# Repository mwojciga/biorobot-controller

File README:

Written by:
Klaudia Trembecka
Maciej Wójciga

Copyright 2013

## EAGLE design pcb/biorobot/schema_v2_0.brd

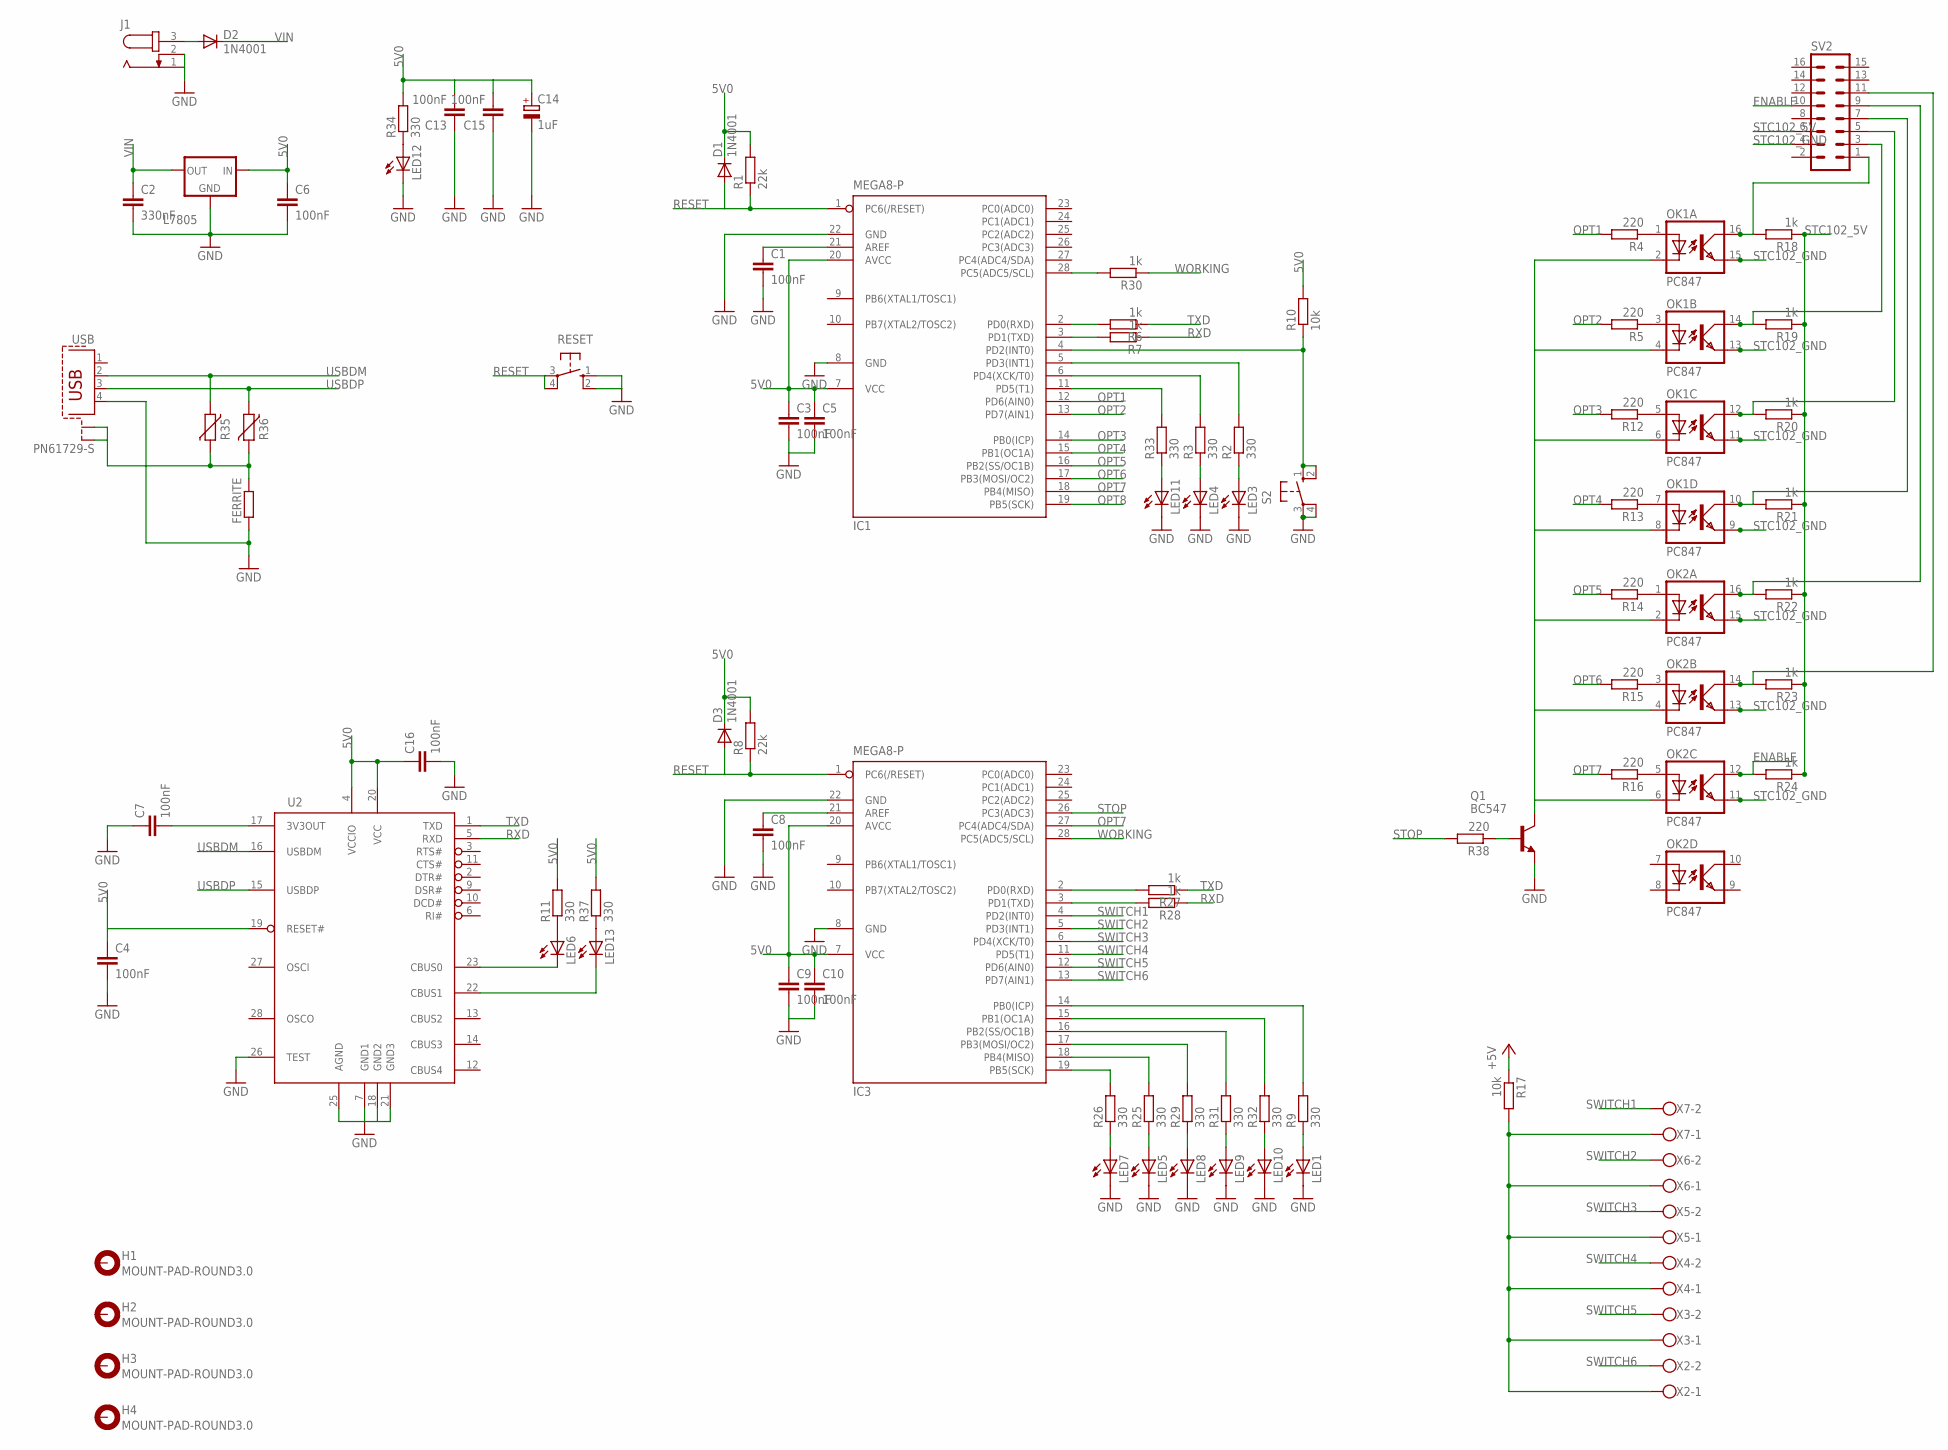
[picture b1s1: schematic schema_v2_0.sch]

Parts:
C1, C3, C5, C6, C8, C9, C10, C13, C15: 100nF; C025-025X050
C2: 330nF; C025-025X050
C4, C7, C16: 100nF; C0603K
C14: 1uF; E2,5-5
D1, D2, D3: 1N4001; DO41-10
FERRITE: R-EU_M0805; M0805
H1, H2, H3, H4: MOUNT-PAD-ROUND3.0; 3,0-PAD
IC1, IC3: MEGA8-P; DIL28-3
J1: JACK-PLUG0; SPC4077
L7805: 79XXS
LED1, LED3, LED4, LED5, LED6, LED7, LED8, LED9, LED10, LED11, LED12, LED13: LED3MM
OK1, OK2: PC847; DIL16
Q1: BC547; TO92
R1, R8: 22k; 0207/10
R2, R3, R9, R11, R25, R26, R29, R31, R32, R33, R34, R37: 330; 0207/10
R4, R5, R12, R13, R14, R15, R16, R38: 220; 0207/10
R6, R7, R27, R28, R30: 1k; M1206
R10, R17: 10k; 0207/10
R18, R19, R20, R21, R22, R23, R24: 1k; 0207/10
R35, R36: VARISTORCN0603; CT/CN0603
RESET: 10-XX; B3F-10XX
S2: 10-XX; B3F-10XX
SV2: MA08-2
U2: FT232RL; SSOP28DB
USB: PN61729-S
X2, X3, X4, X5, X6, X7: W237-102

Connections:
5V0: C3.1, C4.1, C5.1, C6.1, C9.1, C10.1, C13.2, C14.+, C15.2, C16.1, D1.C, D3.C, IC1.7 (VCC), IC1.20 (AVCC), IC3.7 (VCC), IC3.20 (AVCC), L7805.IN, R1.2, R8.2, R10.2, R11.2, R34.2, R37.2, U2.4 (VCCIO), U2.19 (RESET#), U2.20 (VCC)
+5V: R17.1
ENABLE: OK2.12 (COL), R24.2, SV2.10
GND: C1.2, C2.2, C3.2, C4.2, C5.2, C6.2, C7.1, C8.2, C9.2, C10.2, C13.1, C14.-, C15.1, C16.2, FERRITE.1, IC1.8 (GND), IC1.22 (GND), IC3.8 (GND), IC3.22 (GND), J1.1, J1.2, L7805.GND, LED1.K (C), LED3.K (C), LED4.K (C), LED5.K (C), LED7.K (C), LED8.K (C), LED9.K (C), LED10.K (C), LED11.K (C), LED12.K (C), Q1.1 (E), RESET.1 (S), RESET.2 (S1), S2.3, S2.4 (P1), U2.7 (GND1), U2.18 (GND2), U2.21 (GND3), U2.25 (AGND), U2.26 (TEST), USB.4
unnamed: LED1.A, R9.1
unnamed: C1.1, IC1.21 (AREF)
unnamed: IC1.6 (PD4(XCK/T0)), R3.2
unnamed: IC1.4 (PD2(INT0)), R10.1, S2.1 (S), S2.2 (S1)
unnamed: LED3.A, R2.1
unnamed: LED4.A, R3.1
unnamed: D2.A, J1.3
unnamed: OK1.16 (COL), R18.2, SV2.1
unnamed: IC1.5 (PD3(INT1)), R2.2
unnamed: OK1.14 (COL), R19.2, SV2.3
unnamed: OK1.12 (COL), R20.2, SV2.5
unnamed: OK1.10 (COL), R21.2, SV2.7
unnamed: OK2.16 (COL), R22.2, SV2.9
unnamed: OK2.14 (COL), R23.2, SV2.11
unnamed: C8.1, IC3.21 (AREF)
unnamed: LED6.K (C), U2.23 (CBUS0)
unnamed: LED13.K (C), U2.22 (CBUS1)
unnamed: LED6.A, R11.1
unnamed: IC3.14 (PB0(ICP)), R9.2
unnamed: IC1.28 (PC5(ADC5/SCL)), R30.2
unnamed: OK1.2 (C), OK1.4 (C), OK1.6 (C), OK1.8 (C), OK2.2 (C), OK2.4 (C), OK2.6 (C), Q1.3 (C)
unnamed: Q1.2 (B), R38.1
unnamed: IC1.2 (PD0(RXD)), R6.2
unnamed: IC1.3 (PD1(TXD)), R7.2
unnamed: OK1.1 (A), R4.1
unnamed: OK1.3 (A), R5.1
unnamed: OK1.5 (A), R12.1
unnamed: OK1.7 (A), R13.1
unnamed: OK2.1 (A), R14.1
unnamed: OK2.3 (A), R15.1
unnamed: OK2.5 (A), R16.1
unnamed: LED5.A, R25.1
unnamed: R17.2, X2.1, X3.1, X4.1, X5.1, X6.1, X7.1
unnamed: LED7.A, R26.1
unnamed: LED8.A, R29.1
unnamed: LED10.A, R32.1
unnamed: IC3.19 (PB5(SCK)), R26.2
unnamed: LED9.A, R31.1
unnamed: IC3.2 (PD0(RXD)), R27.2
unnamed: IC3.3 (PD1(TXD)), R28.2
unnamed: IC3.18 (PB4(MISO)), R25.2
unnamed: IC3.17 (PB3(MOSI/OC2)), R29.2
unnamed: IC3.16 (PB2(SS/OC1B)), R31.2
unnamed: IC3.15 (PB1(OC1A)), R32.2
unnamed: LED11.A, R33.1
unnamed: IC1.11 (PD5(T1)), R33.2
unnamed: LED12.A, R34.1
unnamed: FERRITE.2, R35.2, R36.2, USB.S1, USB.S2
unnamed: LED13.A, R37.1
unnamed: C7.2, U2.17 (3V3OUT)
OPT1: IC1.12 (PD6(AIN0)), R4.2
OPT2: IC1.13 (PD7(AIN1)), R5.2
OPT3: IC1.14 (PB0(ICP)), R12.2
OPT4: IC1.15 (PB1(OC1A)), R13.2
OPT5: IC1.16 (PB2(SS/OC1B)), R14.2
OPT6: IC1.17 (PB3(MOSI/OC2)), R15.2
OPT7: IC1.18 (PB4(MISO)), IC3.27 (PC4(ADC4/SDA)), R16.2
OPT8: IC1.19 (PB5(SCK))
RESET: D1.A, D3.A, IC1.1 (PC6(/RESET)), IC3.1 (PC6(/RESET)), R1.1, R8.1, RESET.3, RESET.4 (P1)
RXD: R7.1, R28.1, U2.5 (RXD)
STC102_5V: R18.1, R19.1, R20.1, R21.1, R22.1, R23.1, R24.1, SV2.6
STC102_GND: OK1.9 (EMIT), OK1.11 (EMIT), OK1.13 (EMIT), OK1.15 (EMIT), OK2.11 (EMIT), OK2.13 (EMIT), OK2.15 (EMIT), SV2.4
STOP: IC3.26 (PC3(ADC3)), R38.2
SWITCH1: IC3.4 (PD2(INT0)), X7.2
SWITCH2: IC3.5 (PD3(INT1)), X6.2
SWITCH3: IC3.6 (PD4(XCK/T0)), X5.2
SWITCH4: IC3.11 (PD5(T1)), X4.2
SWITCH5: IC3.12 (PD6(AIN0)), X3.2
SWITCH6: IC3.13 (PD7(AIN1)), X2.2
TXD: R6.1, R27.1, U2.1 (TXD)
USBDM: R35.1, U2.16 (USBDM), USB.2
USBDP: R36.1, U2.15 (USBDP), USB.3
VIN: C2.1, D2.C, L7805.OUT
WORKING: IC3.28 (PC5(ADC5/SCL)), R30.1

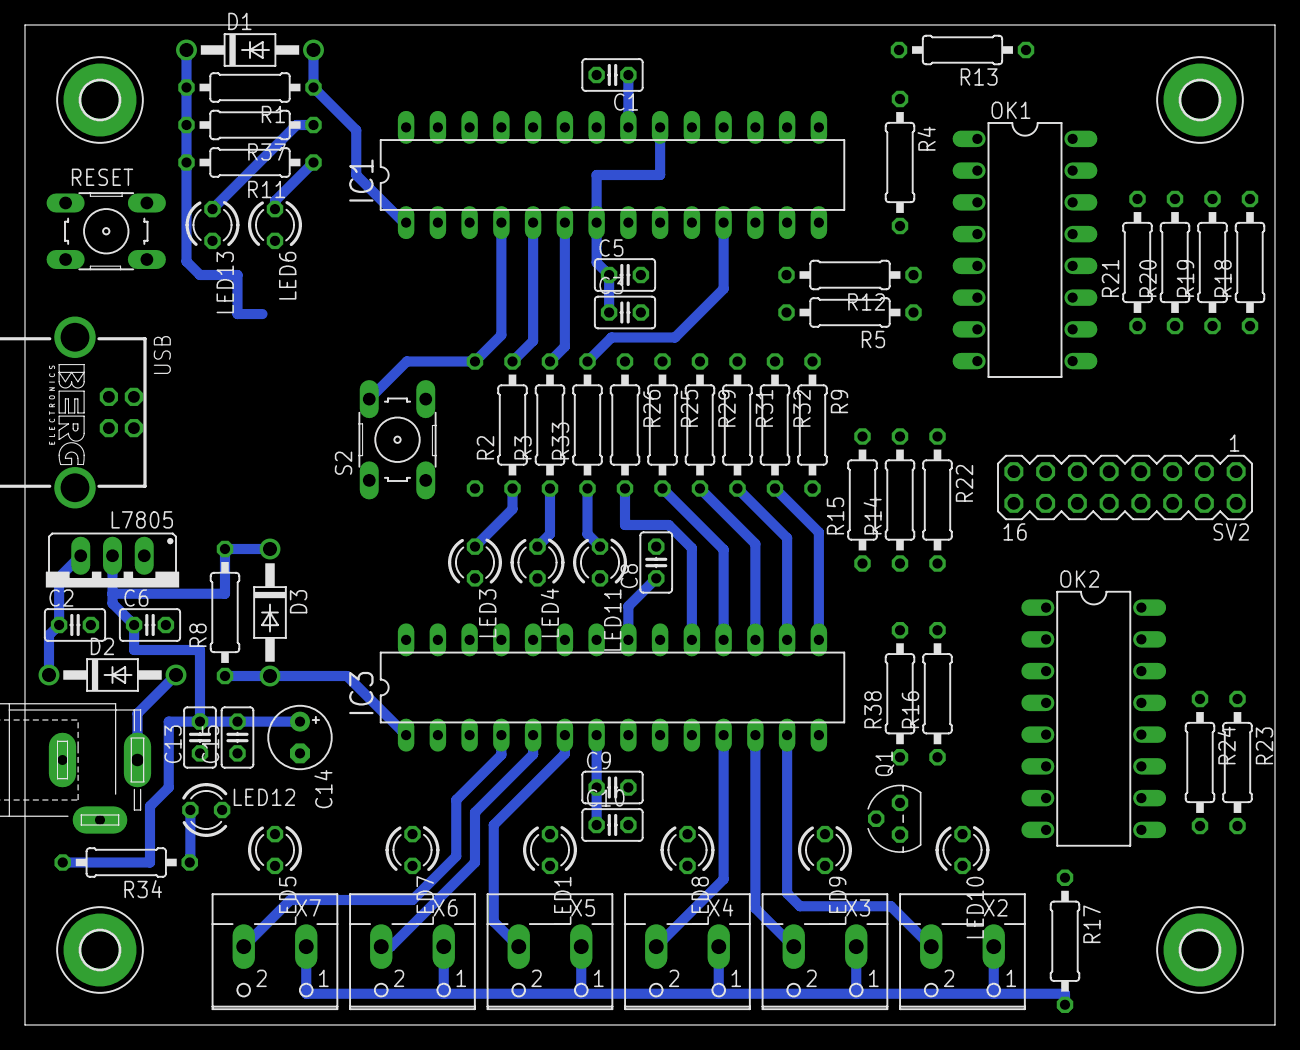
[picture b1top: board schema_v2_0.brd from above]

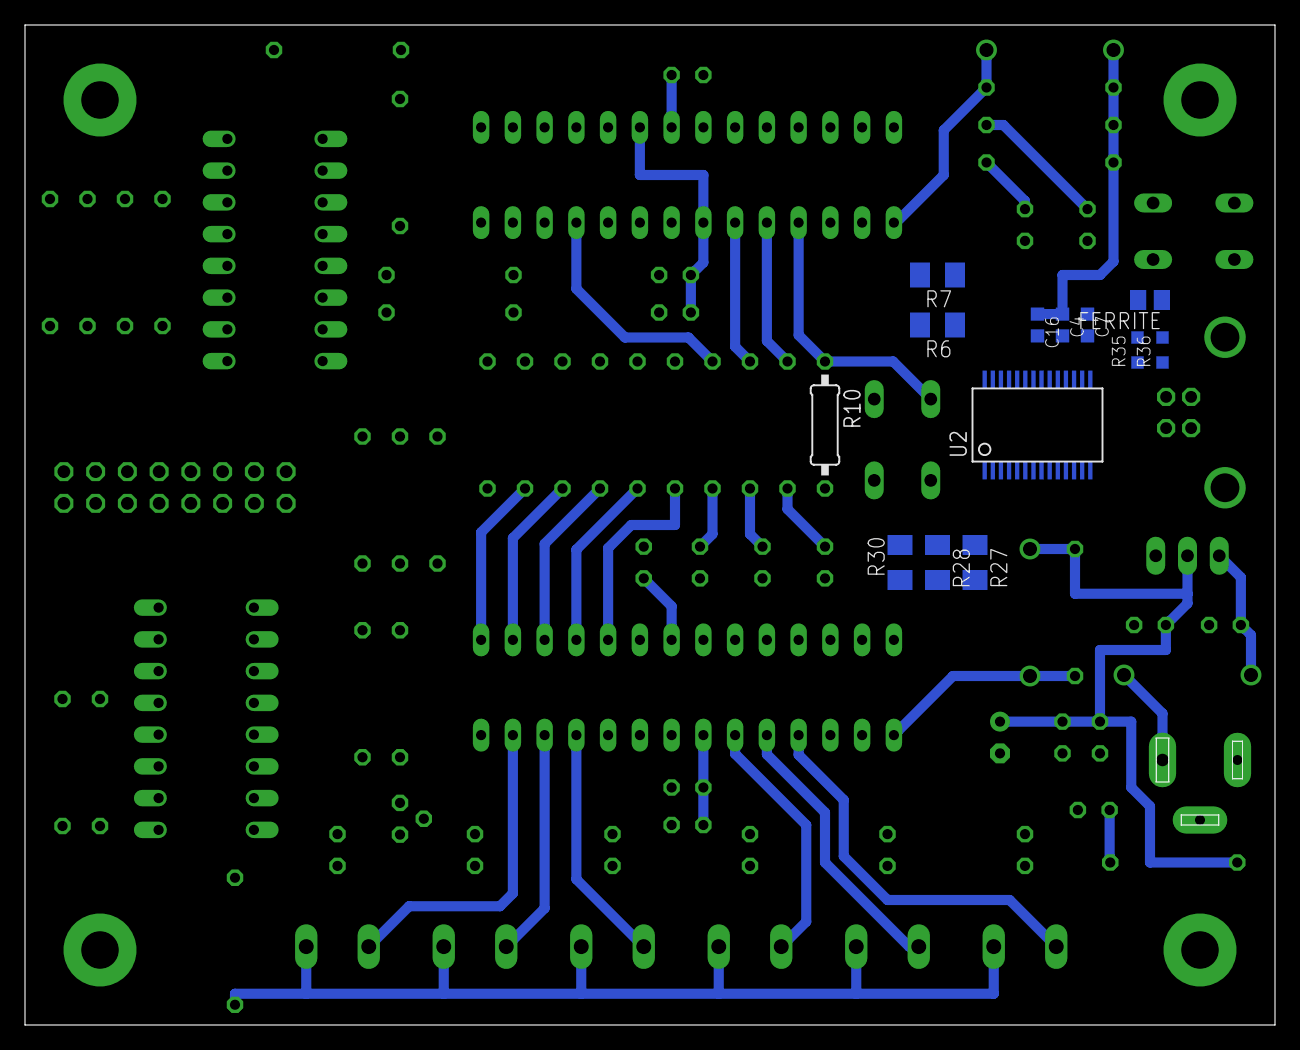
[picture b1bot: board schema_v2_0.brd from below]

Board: 2 copper layers, 100.0 x 80.0 mm, 90 parts (13 on the bottom side), 76 nets.

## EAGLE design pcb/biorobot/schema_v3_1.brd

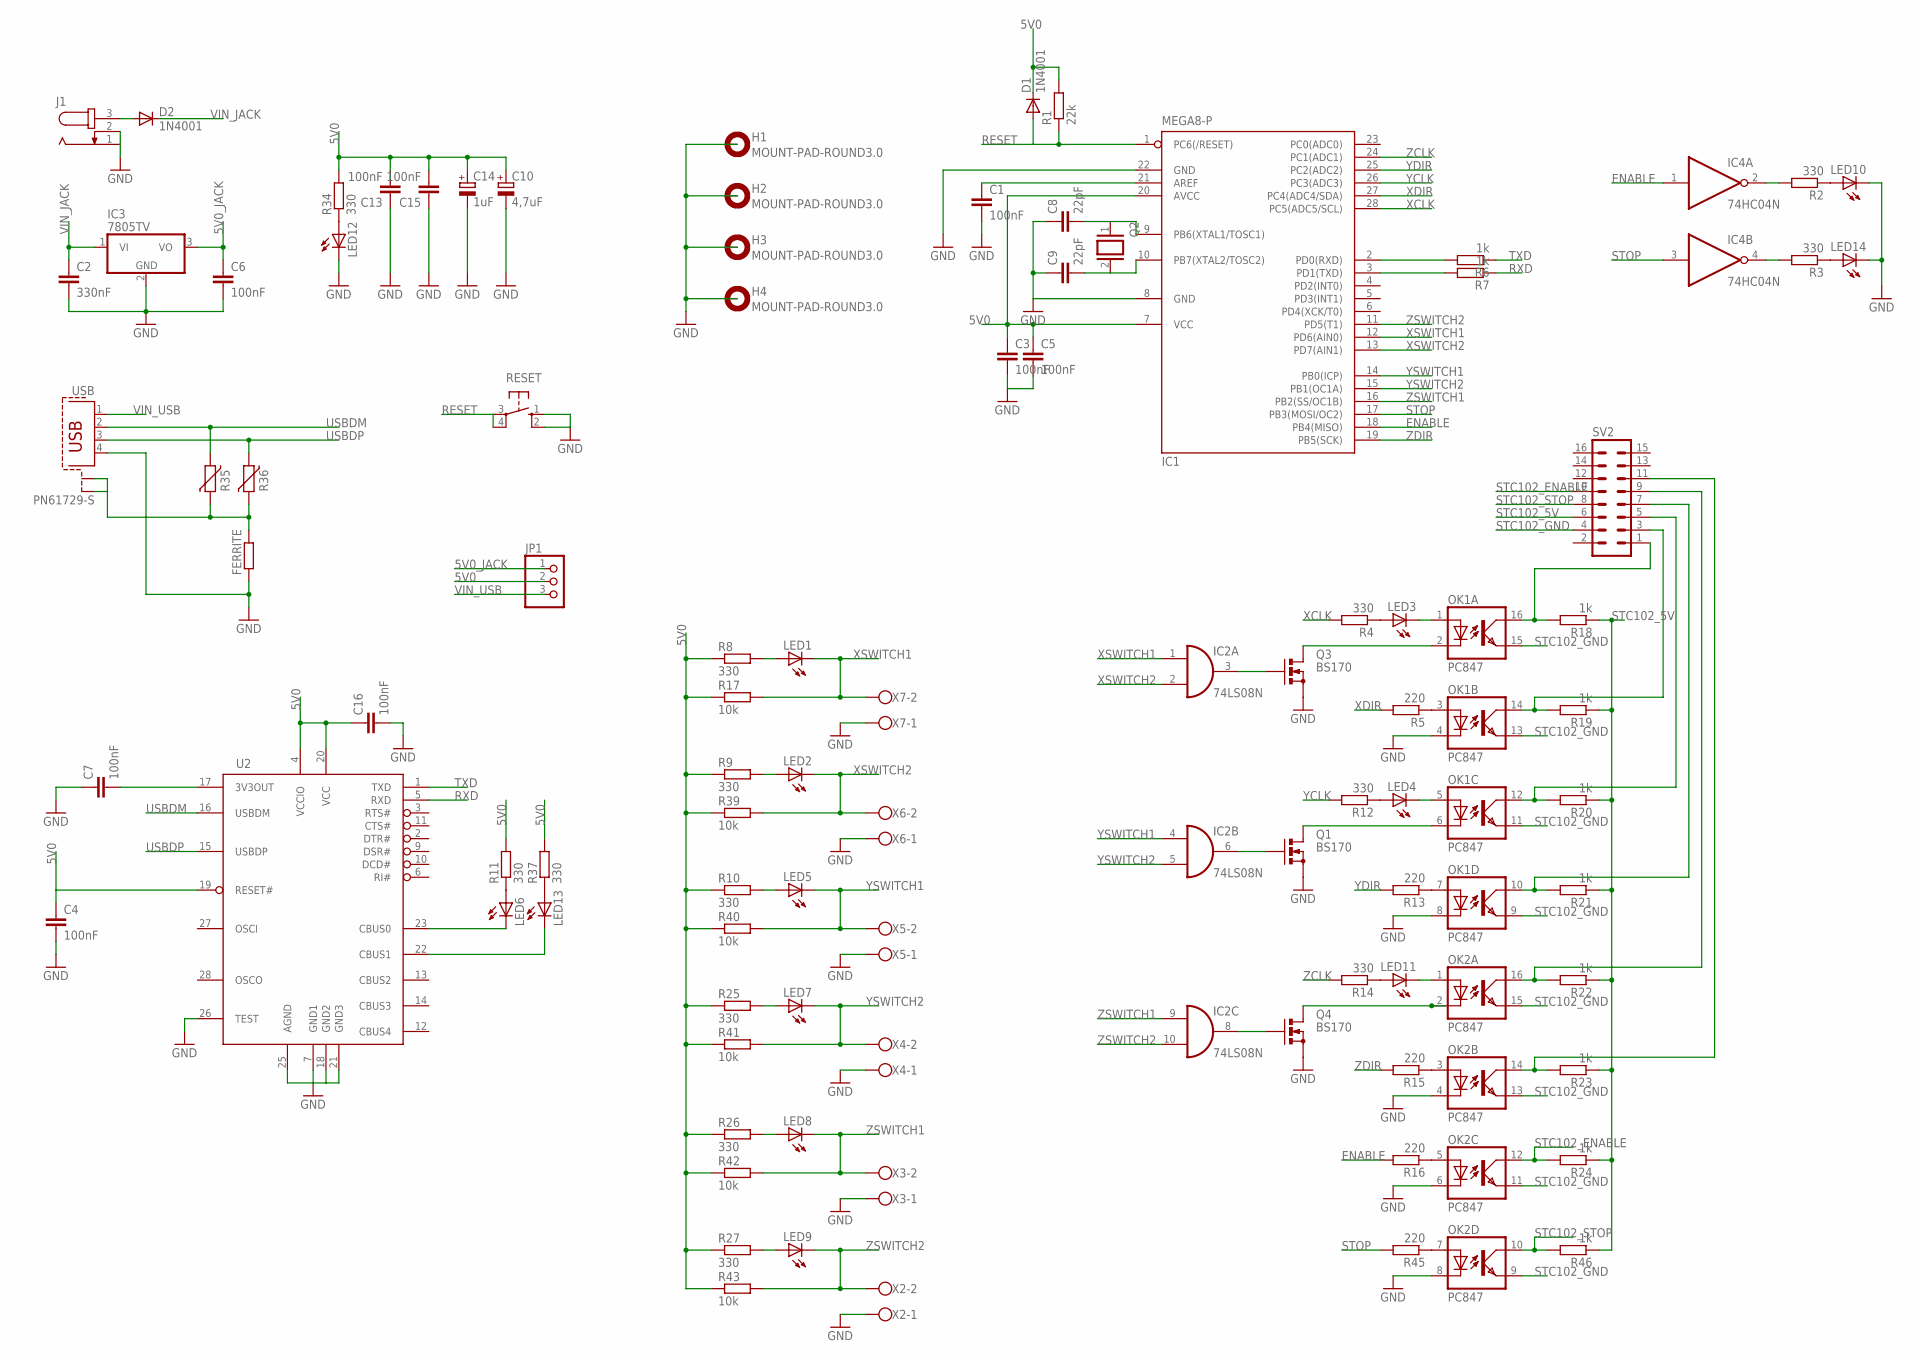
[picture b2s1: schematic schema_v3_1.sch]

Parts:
C1: 100nF; C0805
C2: 330nF; C025-025X050
C3, C5, C6, C13, C15: 100nF; C025-025X050
C4, C7, C16: 100nF; C0603K
C8, C9: 22pF; C025-025X050
C10: 4,7uF; E2,5-5
C14: 1uF; E2,5-5
D1, D2: 1N4001; DO41-10
FERRITE: R-EU_M0805; M0805
H1, H2, H3, H4: MOUNT-PAD-ROUND3.0; 3,0-PAD
IC1: MEGA8-P; DIL28-3
IC2: 74LS08N; DIL14
IC3: 7805TV; TO220V
IC4: 74HC04N; DIL14
J1: JACK-PLUG0; SPC4077
JP1: PINHD-1X3; 1X03
LED1, LED2, LED3, LED4, LED5, LED6, LED7, LED8, LED9, LED10, LED11, LED12, LED13, LED14: LED3MM
OK1, OK2: PC847; DIL16
Q1, Q3, Q4: BS170; SOT54E
Q2: XTAL/S; QS
R1: 22k; 0207/10
R2, R3, R4, R8, R9, R10, R11, R12, R14, R25, R26, R27, R34, R37: 330; 0207/10
R5, R13, R15, R16, R45: 220; 0207/10
R6, R7, R18, R19, R20, R21, R22, R23, R24, R46: 1k; 0207/10
R17, R39, R40, R41, R42, R43: 10k; 0207/10
R35, R36: VARISTORCN0603; CT/CN0603
RESET: 10-XX; B3F-10XX
SV2: MA08-2
U2: FT232RL; SSOP28DB
USB: PN61729-S
X2, X3, X4, X5, X6, X7: W237-102

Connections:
5V0: C3.1, C4.1, C5.1, C10.+, C13.2, C14.+, C15.2, C16.1, D1.C, IC1.7 (VCC), IC1.20 (AVCC), JP1.2, R1.2, R8.1, R9.1, R10.1, R11.2, R17.1, R25.1, R26.1, R27.1, R34.2, R37.2, R39.1, R40.1, R41.1, R42.1, R43.1, U2.4 (VCCIO), U2.19 (RESET#), U2.20 (VCC)
5V0_JACK: C6.1, IC3.3 (VO), JP1.1
ENABLE: IC1.18 (PB4(MISO)), IC4.1 (I), R16.2
GND: C1.2, C2.2, C3.2, C4.2, C5.2, C6.2, C7.1, C8.1, C9.1, C10.-, C13.1, C14.-, C15.1, C16.2, FERRITE.1, IC1.8 (GND), IC1.22 (GND), IC2.7 (GND), IC3.2 (GND), IC4.7 (GND), J1.1, J1.2, LED10.K (C), LED12.K (C), LED14.K (C), OK1.4 (C), OK1.8 (C), OK2.4 (C), OK2.6 (C), OK2.8 (C), Q1.S, Q3.S, Q4.S, RESET.1 (S), RESET.2 (S1), U2.7 (GND1), U2.18 (GND2), U2.21 (GND3), U2.25 (AGND), U2.26 (TEST), USB.4, X2.1, X3.1, X4.1, X5.1, X6.1, X7.1
unnamed: LED3.A, R4.1
unnamed: LED1.A, R8.2
unnamed: C1.1, IC1.21 (AREF)
unnamed: OK2.7 (A), R45.1
unnamed: OK1.2 (C), Q3.D
unnamed: LED4.A, R12.1
unnamed: LED11.A, R14.1
unnamed: D2.A, J1.3
unnamed: OK1.16 (COL), R18.2, SV2.1
unnamed: OK2.5 (A), R16.1
unnamed: OK1.14 (COL), R19.2, SV2.3
unnamed: OK1.12 (COL), R20.2, SV2.5
unnamed: OK1.10 (COL), R21.2, SV2.7
unnamed: OK2.16 (COL), R22.2, SV2.9
unnamed: OK2.14 (COL), R23.2, SV2.11
unnamed: LED2.A, R9.2
unnamed: LED6.K (C), U2.23 (CBUS0)
unnamed: LED13.K (C), U2.22 (CBUS1)
unnamed: LED6.A, R11.1
unnamed: LED10.A, R2.1
unnamed: IC2.3 (O), Q3.G
unnamed: LED14.A, R3.1
unnamed: LED5.A, R10.2
unnamed: LED7.A, R25.2
unnamed: IC1.2 (PD0(RXD)), R6.2
unnamed: IC1.3 (PD1(TXD)), R7.2
unnamed: LED8.A, R26.2
unnamed: LED9.A, R27.2
unnamed: C8.2, IC1.9 (PB6(XTAL1/TOSC1)), Q2.1
unnamed: OK1.3 (A), R5.1
unnamed: LED4.K (C), OK1.5 (A)
unnamed: OK1.7 (A), R13.1
unnamed: LED3.K (C), OK1.1 (A)
unnamed: OK2.3 (A), R15.1
unnamed: C9.2, IC1.10 (PB7(XTAL2/TOSC2)), Q2.2
unnamed: OK1.6 (C), Q1.D
unnamed: OK2.2 (C), Q4.D
unnamed: IC2.8 (O), Q4.G
unnamed: IC2.6 (O), Q1.G
unnamed: LED11.K (C), OK2.1 (A)
unnamed: IC4.2 (O), R2.2
unnamed: IC4.4 (O), R3.2
unnamed: LED12.A, R34.1
unnamed: FERRITE.2, R35.2, R36.2, USB.S1, USB.S2
unnamed: LED13.A, R37.1
unnamed: C7.2, U2.17 (3V3OUT)
RESET: D1.A, IC1.1 (PC6(/RESET)), R1.1, RESET.3, RESET.4 (P1)
RXD: R7.1, U2.5 (RXD)
STC102_5V: R18.1, R19.1, R20.1, R21.1, R22.1, R23.1, R24.1, R46.1, SV2.6
STC102_ENABLE: OK2.12 (COL), R24.2, SV2.10
STC102_GND: OK1.9 (EMIT), OK1.11 (EMIT), OK1.13 (EMIT), OK1.15 (EMIT), OK2.9 (EMIT), OK2.11 (EMIT), OK2.13 (EMIT), OK2.15 (EMIT), SV2.4
STC102_STOP: OK2.10 (COL), R46.2, SV2.8
STOP: IC1.17 (PB3(MOSI/OC2)), IC4.3 (I), R45.2
TXD: R6.1, U2.1 (TXD)
USBDM: R35.1, U2.16 (USBDM), USB.2
USBDP: R36.1, U2.15 (USBDP), USB.3
VCC: IC2.14 (VCC), IC4.14 (VCC)
VIN_JACK: C2.1, D2.C, IC3.1 (VI)
VIN_USB: JP1.3, USB.1
XCLK: IC1.28 (PC5(ADC5/SCL)), R4.2
XDIR: IC1.27 (PC4(ADC4/SDA)), R5.2
XSWITCH1: IC1.12 (PD6(AIN0)), IC2.1 (I0), LED1.K (C), R17.2, X7.2
XSWITCH2: IC1.13 (PD7(AIN1)), IC2.2 (I1), LED2.K (C), R39.2, X6.2
YCLK: IC1.26 (PC3(ADC3)), R12.2
YDIR: IC1.25 (PC2(ADC2)), R13.2
YSWITCH1: IC1.14 (PB0(ICP)), IC2.4 (I0), LED5.K (C), R40.2, X5.2
YSWITCH2: IC1.15 (PB1(OC1A)), IC2.5 (I1), LED7.K (C), R41.2, X4.2
ZCLK: IC1.24 (PC1(ADC1)), R14.2
ZDIR: IC1.19 (PB5(SCK)), R15.2
ZSWITCH1: IC1.16 (PB2(SS/OC1B)), IC2.9 (I0), LED8.K (C), R42.2, X3.2
ZSWITCH2: IC1.11 (PD5(T1)), IC2.10 (I1), LED9.K (C), R43.2, X2.2

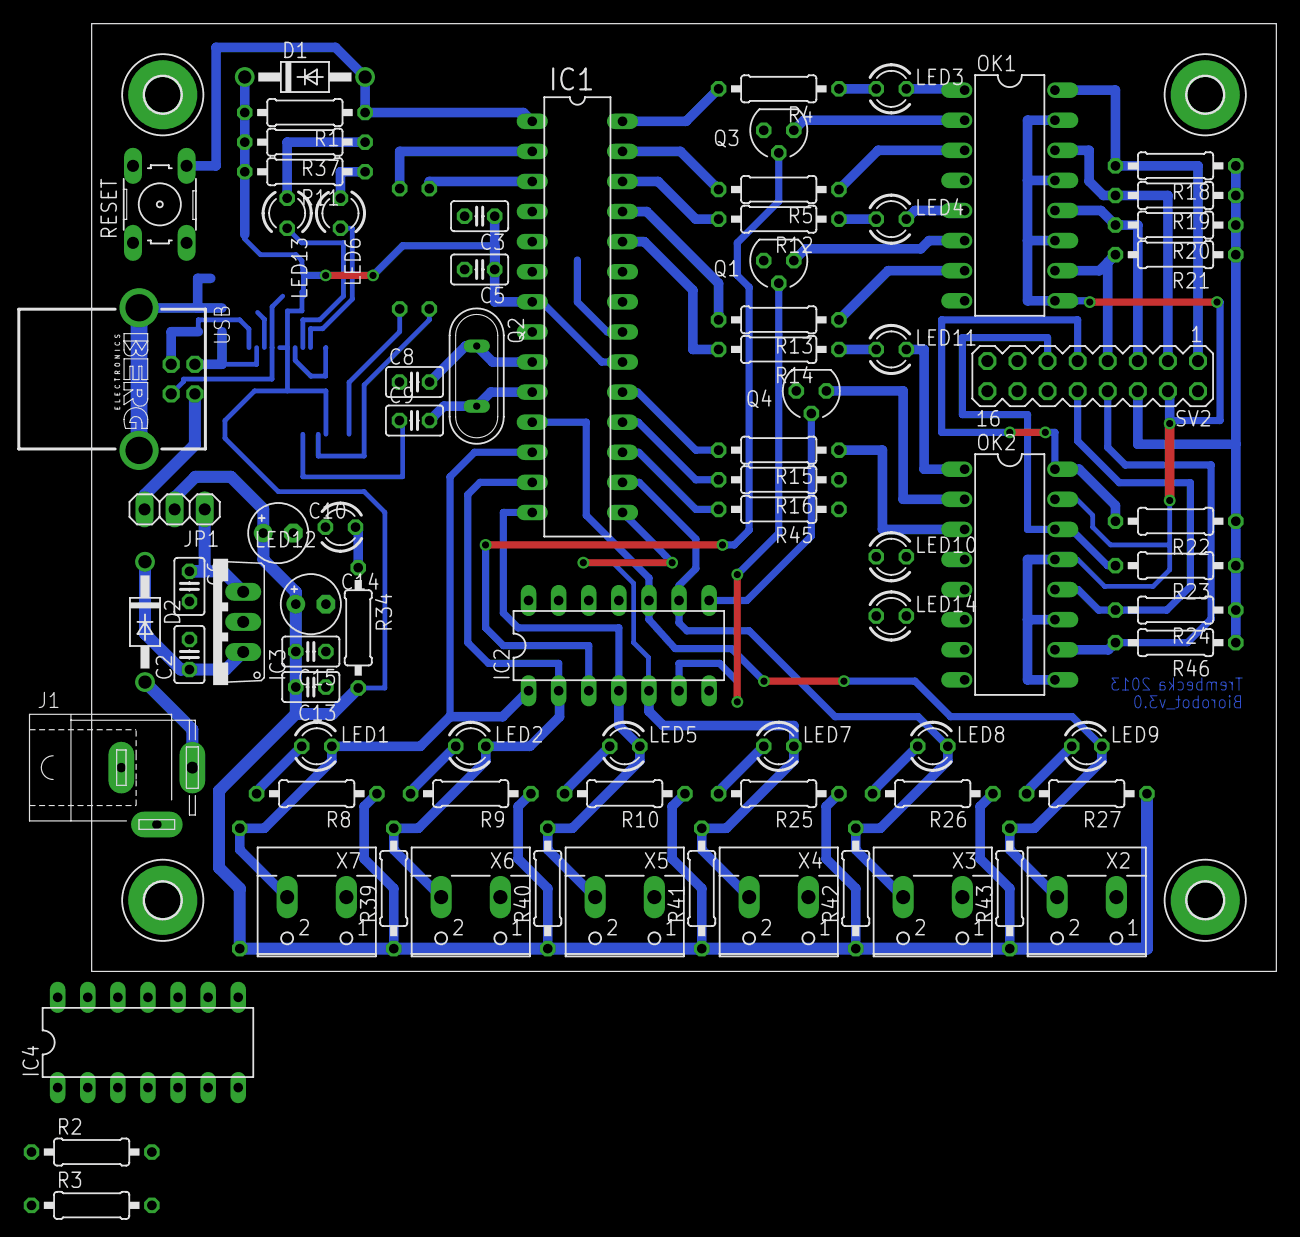
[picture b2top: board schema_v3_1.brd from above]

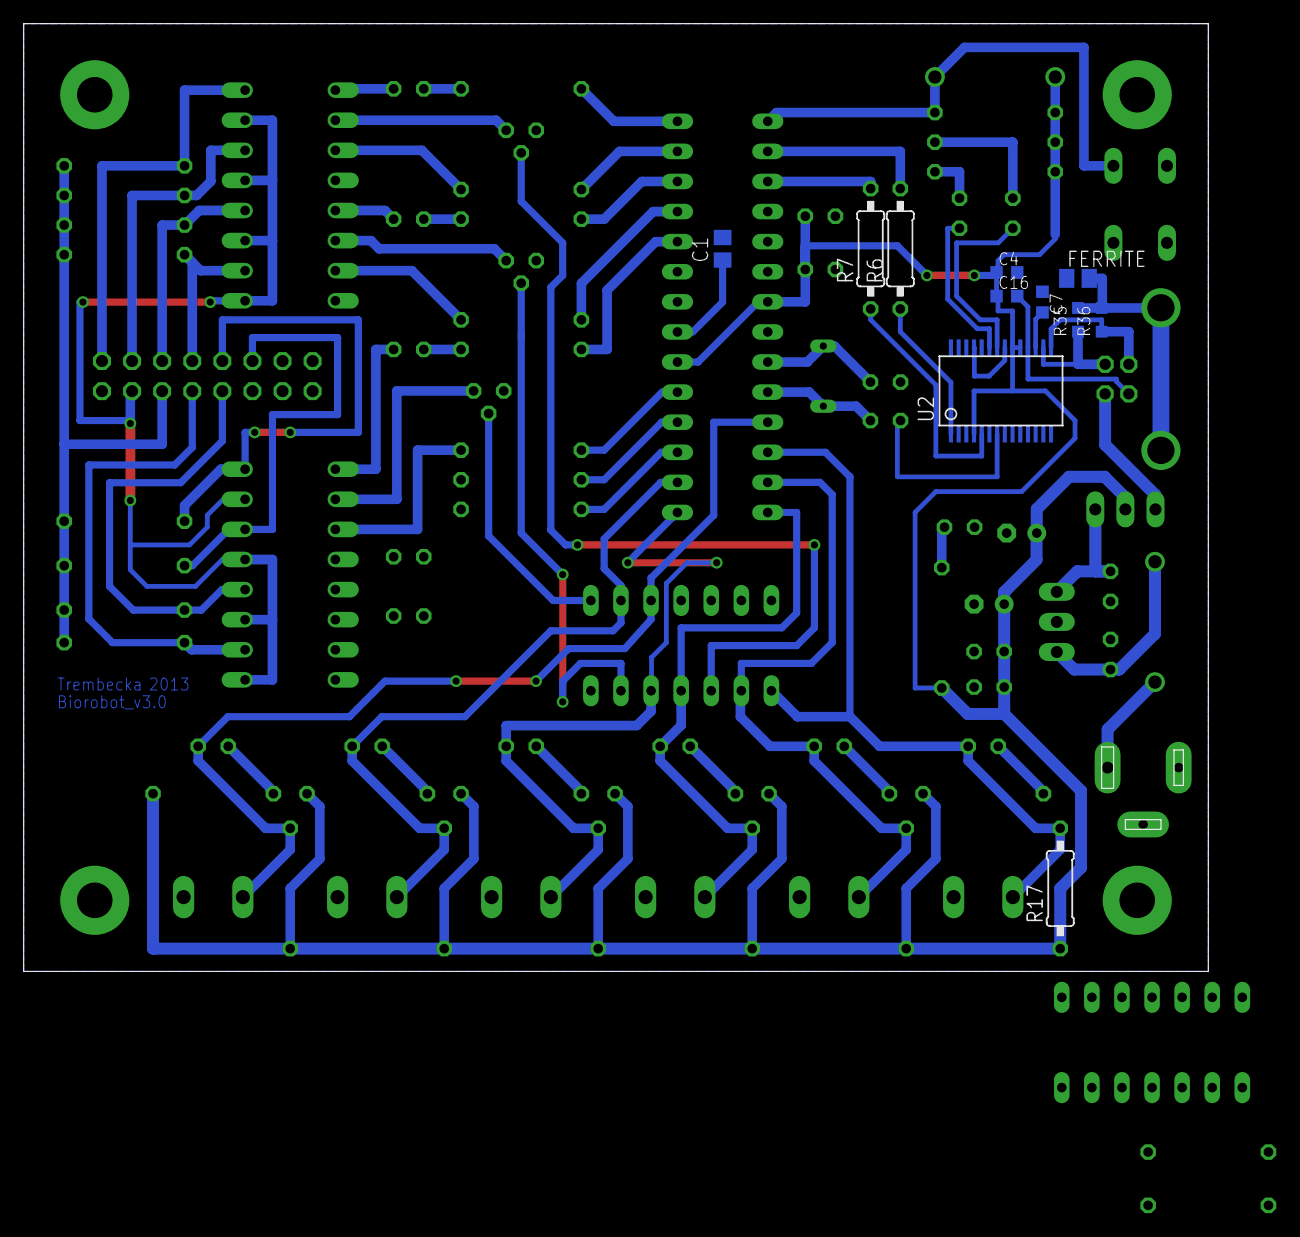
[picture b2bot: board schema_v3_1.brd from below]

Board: 2 copper layers, 100.0 x 80.0 mm, 95 parts (11 on the bottom side), 75 nets.

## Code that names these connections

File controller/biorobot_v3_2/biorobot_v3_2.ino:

/*
Klaudia Trembecka & Maciej Wojciga
Last update: 20130310
A software for uC, used to aquire commands from USB (from java app),
and use them to move the robot motors (x, y, z).
*/

/* 
CHANGELOG
3.2: Changed some read/write functions to bitmath style.
     Also, int to long in x, y, z. Added timing after all motors finish work.
3.1: Changed millis to micros to fasten up the motors.
*/

/*
TODO
1. Put the motors into LOW after work;
2. Check if it accepts smal numbers.
3. X and Y in one loop! The frequency between X, Y and Z are different! Why?
*/

int place = 0;
int i = 0;
int j = 0;
int started = 0;
int timeout = 1000; 

char a;

/*
This arrays are 1 char larger, because they should
have also place for the terminating \0 for atoi method.
*/
char serialReadString[28]; //20
char xarray[4]; 
char yarray[4];
char zarray[4];
char tarray[4];

/* Used only for creating x, y, z arrays */
byte b = 0;
byte c = 0;
byte d = 0;
byte f = 0;

/* Initializing variables */
byte v = 0;
long x = 0;
long y = 0;
long z = 0;
int t = 0;
byte e = 0;
byte xdir = 0;
byte ydir = 0;
byte zdir = 0;
long waited = 0;
byte waiting = 0;

/* Variables connected with motors */
long xmicros = 0;
long xmov = 0;
byte xstate = 0;
byte xstarted = 0;
long ymicros = 0;
long ymov = 0;
byte ystate = 0;
byte ystarted = 0;
long zmicros = 0;
long zmov = 0;
byte zstate = 0;
byte zstarted = 0;
byte allfinished = 0;
long tmillis = 0;

/* Limit switches */
byte xlimit = 0;
byte ylimit = 0;
byte zlimit = 0;
byte x2limit = 0;
byte y2limit = 0;
byte z2limit = 0;

void setup() {
  Serial.begin(9600); // it must be the same as in our java app.
  /* Specifing pins connected with our motor controller.*/
  pinMode(12, OUTPUT); // enable.
  pinMode(11, OUTPUT); // stop.
  pinMode(A5, OUTPUT); // x clock.
  pinMode(A3, OUTPUT); // y clock.
  pinMode(A1, OUTPUT); // z clock.
  pinMode(A4, OUTPUT); // x direction.
  pinMode(A2, OUTPUT); // y direction.
  pinMode(13, OUTPUT); // z direction.
  pinMode(6, INPUT); // x limit.
  pinMode(7, INPUT); // x limit.
  pinMode(8, INPUT); // y limit.
  pinMode(9, INPUT); // y limit.
  pinMode(10, INPUT); // z limit.
  pinMode(5, INPUT); // z limit.
  /* By default all pins should be LOW */
  digitalWrite(12, HIGH); // block motors by default
  digitalWrite(11, LOW); // stop.
  digitalWrite(A5, LOW);
  digitalWrite(A3, LOW);
  digitalWrite(A1, LOW);
  digitalWrite(A4, LOW);
  digitalWrite(A2, LOW);
  digitalWrite(13, LOW);
}

void loop() {
  /* LIMIT SWITCHES */
  xlimit = PIND & ( 1 << 6 ); //digitalRead(6);
  x2limit = PIND & ( 1 << 7 ); //digitalRead(7);
  ylimit = PIND & ( 1 << 8 ); //digitalRead(8);
  y2limit = PIND & ( 1 << 9 ); //digitalRead(9);
  zlimit = PIND & ( 1 << 10 ); //digitalRead(10);
  z2limit = PIND & ( 1 << 5 ); //digitalRead(5);
  
  if(xlimit == LOW || x2limit == LOW ) {
    x = 0;
    xmov = 0;
    xmicros = 0;
    xstarted = 0;
  }
  if(ylimit == LOW || y2limit == LOW ) {
    y =0;
    ymov = 0;
    ymicros = 0;
    ystarted = 0;
  }
  if(zlimit == LOW || z2limit == LOW ) {
    z =0;
    zmov = 0;
    zmicros = 0;
    zstarted = 0;
  }
  
  /* X AXIS */
  if (xmov < x && micros() - xmicros >= timeout && e != 1 && xlimit != LOW && x2limit != LOW) {
    xmov++;
    xmicros = micros();
    xstate = !xstate;
    xstarted = 1;
    if (xstate == 0){
      PORTC &= ~_BV(PC5);
    } else {
      PORTC |= _BV(PC5);
    }
  }
  if (xmov == x && xstarted == 1) {
    xmov = 0;
    xstarted = 0;
    x = 0;
    Serial.write("XFin;");
  }
  /* Y AXIS */
  if (ymov < y && micros() - ymicros >= timeout && e != 1 && ylimit != LOW && y2limit != LOW) {
    ymov++;
    ymicros = micros();
    ystate = !ystate;
    ystarted = 1;
    if (ystate == 0){
      PORTC &= ~_BV(PC3);
    } else {
      PORTC |= _BV(PC3);
    }
  }
  if (ymov == y && ystarted == 1) {
    ymov = 0;
    ystarted = 0;
    y = 0;
    Serial.write("YFin;");
  }
  /* Z AXIS */
  if (zmov < z && micros() - zmicros >= timeout && e != 1 && xstarted == 0 && ystarted == 0 && zlimit != LOW && z2limit != LOW) {
    zmov++;
    zmicros = micros();
    zstate = !zstate;
    zstarted = 1;
    if (zstate == 0){
      PORTC &= ~_BV(PC1);
    } else {
      PORTC |= _BV(PC1);
    }
  }
  if (zmov == z && zstarted == 1) {
    zmov = 0;
    zstarted = 0;
    z = 0;
    allfinished = 1;
    Serial.write("ZFin;");
  }
  /* WAIT AFTER ALL MOTORS */
  if (allfinished == 1 && millis() - tmillis >= 10 && waited <= t*100 && t != 0) {
    tmillis = millis();
    waiting = 1;
    waited++;
  }
  if (allfinished == 1 && waited == t*100 && waiting == 1) {
    waiting = 0;
    waited = 0;
    t =0;
    allfinished = 0;
    Serial.write("WFin;");
  }
  
  /*
  The message looks like this:
  Sv9d000x100y200z200t602e0E
  */
  /* Check the incomming message */
  while(Serial.available()) {
    a = Serial.read();
    if(a == 'S') { // beginning of the command.
      started = 1;
    }
    if(a == 'E' && started == 1){ // end of the command.
      place = 0; // reset the place in the array.
      for(i=0; i<=2; i++){
        b = i+8;
        c = i+12;
        d = i+16;
        f = i+20;
        xarray[i]=serialReadString[b];
        yarray[i]=serialReadString[c];
        zarray[i]=serialReadString[d];
        tarray[i]=serialReadString[f];
      }
      v = serialReadString[2]-48; // int = char-48;
      e = serialReadString[24]-48;
      x = atol(xarray)*100;
      y = atol(yarray)*100;
      z = atol(zarray)*100;
      t = atoi(tarray);
      xdir = serialReadString[4]-48;
      ydir = serialReadString[5]-48;
      zdir = serialReadString[6]-48;
      /* Now we have x, y, z, v, e, xdir, ydir, zdir 
      We can end the loop */
      if(e == 0) {
        /* Set ENABLE to LOW to release the motors */
        digitalWrite(12, LOW);
        /* Set STOP to HIGH */
        digitalWrite(11, HIGH);
      } else {
        Serial.print("ERROR!");
        digitalWrite(12, HIGH);
        digitalWrite(11, LOW);
        x = 0;
        xmov = 0;
        xmicros = 0;
        xstarted = 0;
        y =0;
        ymov = 0;
        ymicros = 0;
        ystarted = 0;
        z =0;
        zmov = 0;
        zmicros = 0;
        zstarted = 0;
        digitalWrite(A5, LOW);
        digitalWrite(A3, LOW);
        digitalWrite(A1, LOW);
      }
      if(xdir == 0){
        digitalWrite(A4, LOW);
      }
      if(ydir == 0){
        digitalWrite(A2, LOW);
      }
      if(zdir == 0){
        digitalWrite(13, LOW);
      }
      if(xdir == 1){
        digitalWrite(A4, HIGH);
      }
      if(ydir == 1){
        digitalWrite(A2, HIGH);
      }
      if(zdir == 1){
        digitalWrite(13, HIGH);
      }      
      timeout = 910-v*100;
      started = 0;
    } else {
      if (started == 1){ // the middle of the command.
        serialReadString[place] = a;
        place++; 
      }
    }
  }
 delayMicroseconds(3);
}

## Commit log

2019-10-08 author fixes
2022-07-17 Migrated PCB schema and firmware code from other repo.
2022-07-17 Removed email address from README.
